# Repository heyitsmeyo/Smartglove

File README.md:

# Smartglove
The project is about a smart glove that translates ASL (American sign language ) to text and speech using a machine learning model based on random forest algorithms , the model is deployed on a raspberry pi 4 model B  , the glove comes with a esp32 , five fkex sensors and a module that integrates both gyroscope and accelerometer (MPU6050) 

The dataset used in this project can be found here : https://figshare.com/articles/dataset/ASL-Sensor-Dataglove-Dataset_zip/20031017?file=35776586

# PCBDesign : 

# pcbSchematic :

# if you like the project , you can donate us for more : 

    https://ko-fi.com/heyitsmeyo

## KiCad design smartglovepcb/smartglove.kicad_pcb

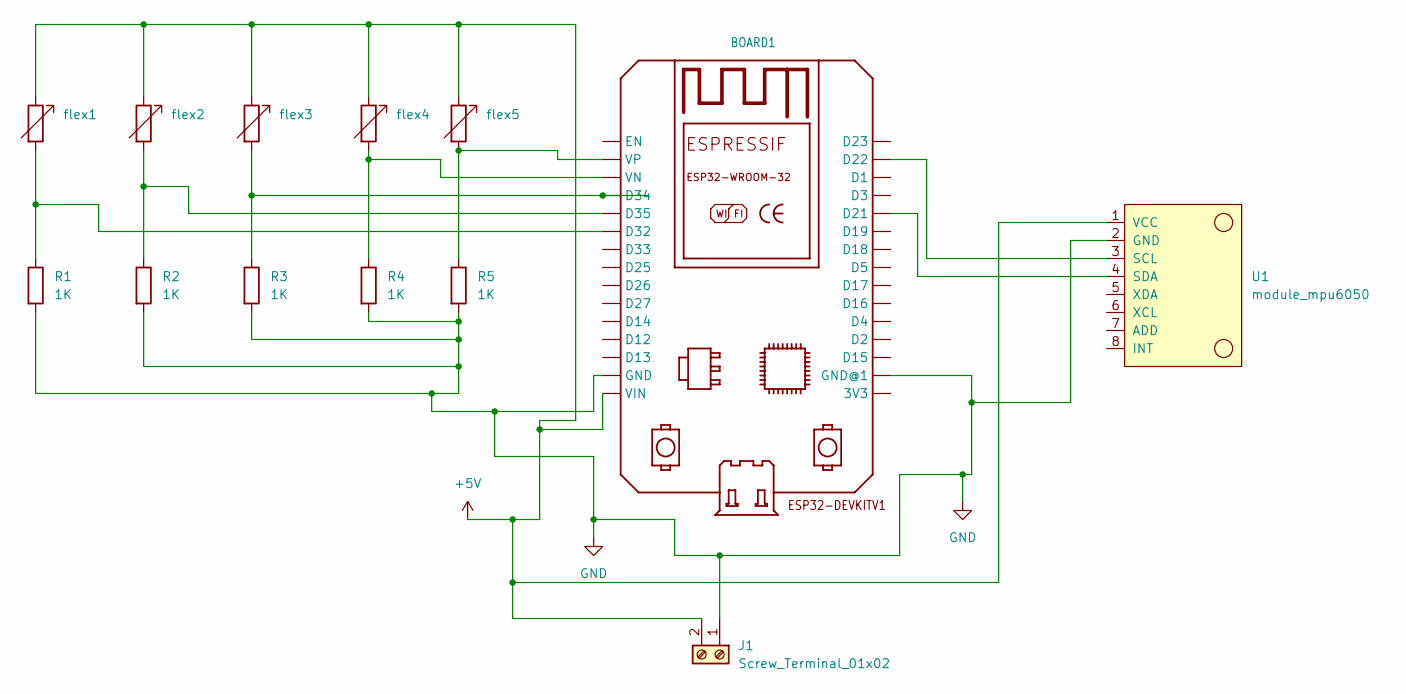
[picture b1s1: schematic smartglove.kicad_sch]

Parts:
BOARD1: ESP32-DEVKITV1
J1: Screw_Terminal_01x02; screwterminal
R1, R2, R3, R4, R5: 1K; R_Axial_DIN0207_L6.3mm_D2.5mm_P7.62mm_Horizontal
U1: module_mpu6050
flex1, flex2, flex3, flex4, flex5: R_Variable; JST_EH_B2B-EH-A_1x02_P2.50mm_Vertical

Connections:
+5V: BOARD1.VIN, J1.2, flex1.1, flex2.1, flex3.1, flex4.1, flex5.1; also elsewhere on the board
GND: BOARD1.GND, BOARD1.GND@1, J1.1, R1.2, R2.2, R3.2, R4.2, R5.2; also elsewhere on the board
unnamed: BOARD1.D32, R1.1, flex1.2
unnamed: BOARD1.D34, R3.1, flex3.2
unnamed: BOARD1.D35, R2.1, flex2.2
unnamed: BOARD1.VN, R4.1, flex4.2
unnamed: BOARD1.VP, R5.1, flex5.2
unnamed 7: BOARD1.D22; also elsewhere on the board
unnamed 8: BOARD1.D21; also elsewhere on the board

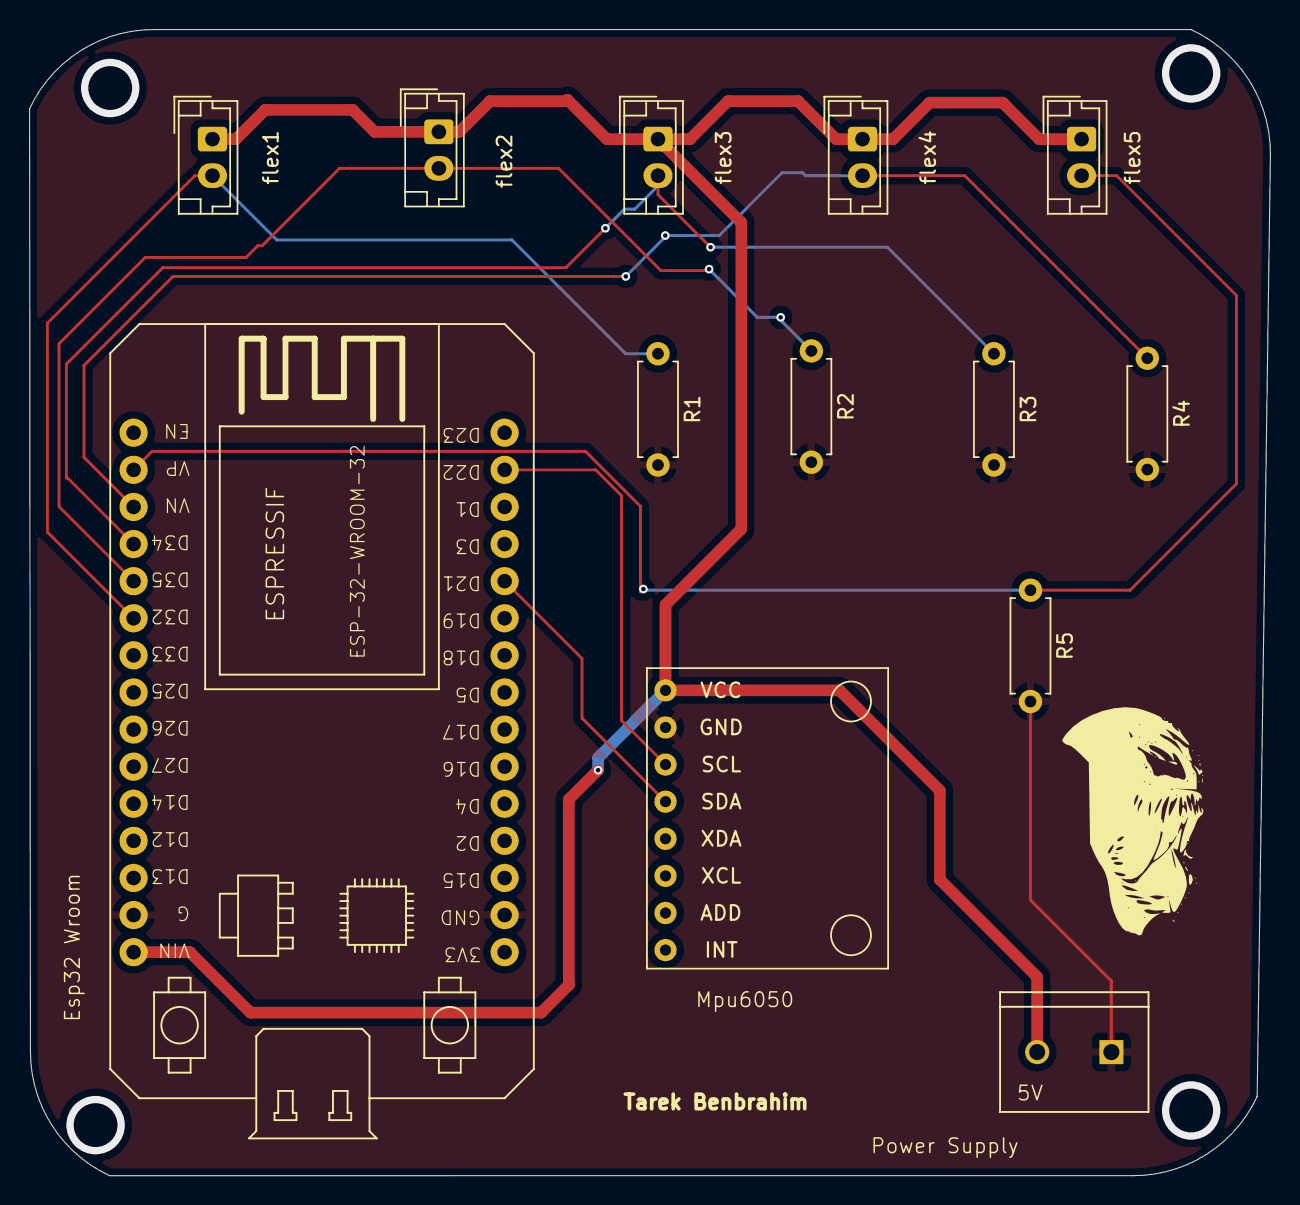
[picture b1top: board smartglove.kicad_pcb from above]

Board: 2 copper layers, 84.9 x 78.5 mm, 13 parts (0 on the bottom side), 9 nets.

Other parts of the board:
U2: module_mpu6050

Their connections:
+5V: U2.1 (VCC); also elsewhere on the board
GND: U2.2 (GND); also elsewhere on the board
unnamed 7: U2.3 (SCL); also elsewhere on the board
unnamed 8: U2.4 (SDA); also elsewhere on the board
